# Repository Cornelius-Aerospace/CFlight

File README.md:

# CFlight
Experimental rocketry controller based on the esp8266 (esp01s), MPU6050 (accelerometer & gyroscope), Barometer (altitude) and small LiPo

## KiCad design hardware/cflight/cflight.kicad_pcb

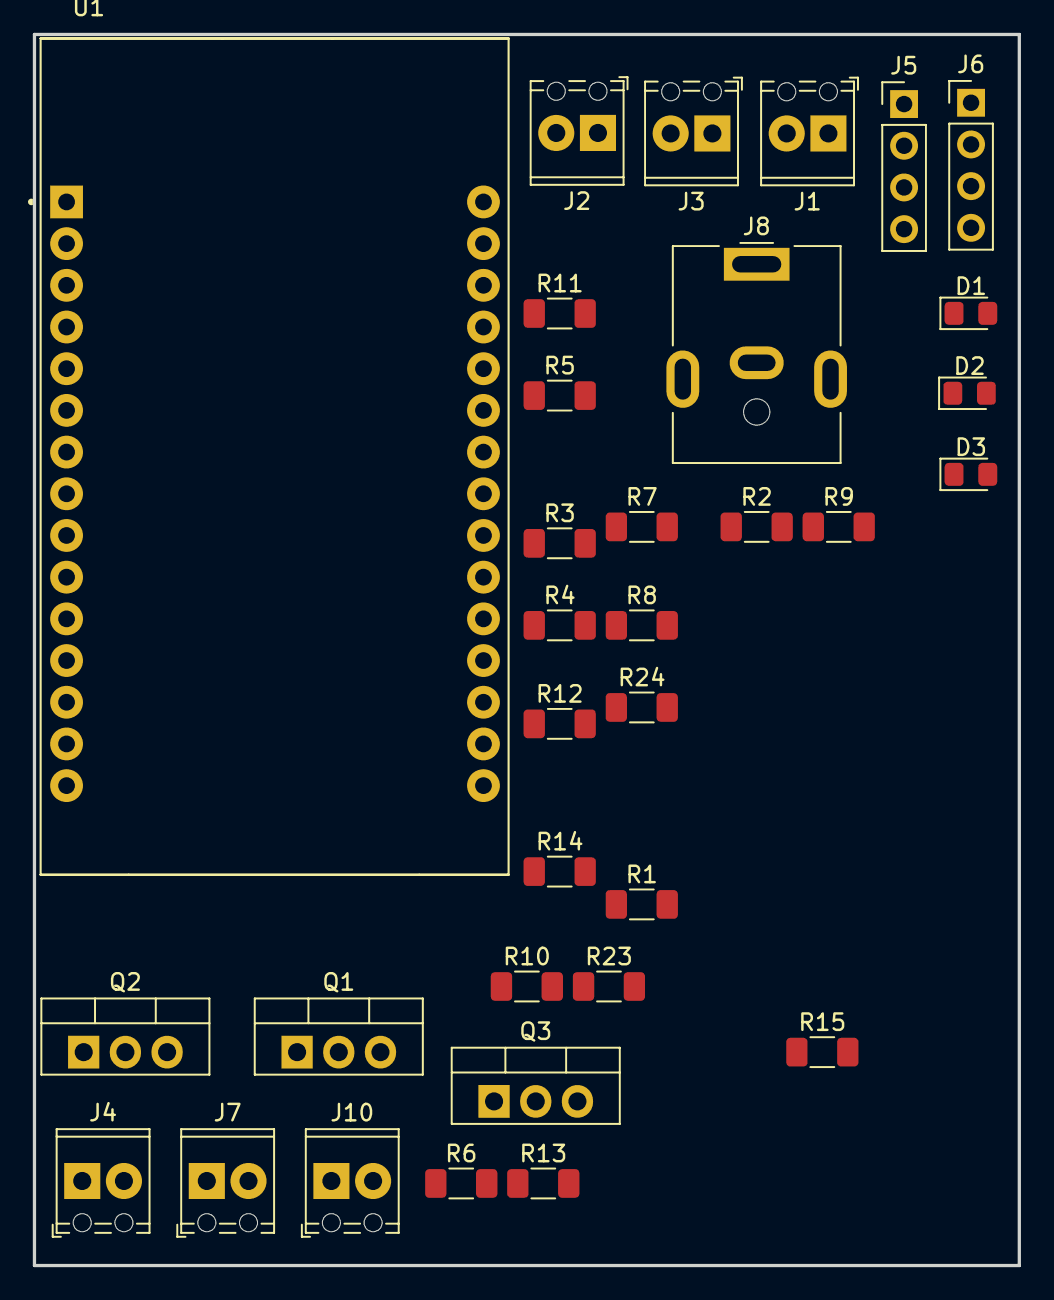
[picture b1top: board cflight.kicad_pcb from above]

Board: 2 copper layers, 60.0 x 75.0 mm, 33 parts (0 on the bottom side), 26 nets, no tracks yet.

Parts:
D1: Armed; LED_0805_2012Metric_Pad1.15x1.40mm_HandSolder
D2: Error; LED_0805_2012Metric_Pad1.15x1.40mm_HandSolder
D3: Status; LED_0805_2012Metric_Pad1.15x1.40mm_HandSolder
J1: 7.2v; TerminalBlock_Phoenix_MPT-0,5-2-2.54_1x02_P2.54mm_Horizontal
J2: I2C; TerminalBlock_Phoenix_MPT-0,5-2-2.54_1x02_P2.54mm_Horizontal
J3: 3.3v; TerminalBlock_Phoenix_MPT-0,5-2-2.54_1x02_P2.54mm_Horizontal
J4: CH_{1}; TerminalBlock_Phoenix_MPT-0,5-2-2.54_1x02_P2.54mm_Horizontal
J5: GPS; PinHeader_1x04_P2.54mm_Vertical
J6: GPRS; PinHeader_1x04_P2.54mm_Vertical
J7: CH_{3}; TerminalBlock_Phoenix_MPT-0,5-2-2.54_1x02_P2.54mm_Horizontal
J8: Barrel_Jack_Switch; BarrelJack_CUI_PJ-063AH_Horizontal
J10: CH_{2}; TerminalBlock_Phoenix_MPT-0,5-2-2.54_1x02_P2.54mm_Horizontal
Q1, Q2, Q3: TIP122; TO-220-3_Vertical
R1, R6, R12: 10k; R_1206_3216Metric_Pad1.30x1.75mm_HandSolder
R2: 18k; R_1206_3216Metric_Pad1.30x1.75mm_HandSolder
R3, R4, R11: 5k; R_1206_3216Metric_Pad1.30x1.75mm_HandSolder
R5: 12k; R_1206_3216Metric_Pad1.30x1.75mm_HandSolder
R7, R15: 80; R_1206_3216Metric_Pad1.30x1.75mm_HandSolder
R8, R14, R24: 470; R_1206_3216Metric_Pad1.30x1.75mm_HandSolder
R9: 50; R_1206_3216Metric_Pad1.30x1.75mm_HandSolder
R10, R13, R23: 4k7; R_1206_3216Metric_Pad1.30x1.75mm_HandSolder
U1: ESP32-DEVKIT-V1; MODULE_ESP32_DEVKIT_V1

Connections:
+3.3V: J3.1, J5.1, J6.1, U1.1 (3V3)
BATT_{check}: R2.2, R5.2, U1.25 (D27)
Batt_{gnd}: D1.1 (K), D2.1 (K), D3.1 (K), J1.2, J3.2, J5.2, J6.2, Q1.3 (E), Q2.3 (E), Q3.3 (E), R3.1, R4.1, R5.1, R10.2, R11.1, R13.2, R23.2, U1.2 (GND), U1.29 (GND)
CH_{1}^{fire}: R8.2, U1.21 (D32)
CH_{1}^{test}: R1.1, R3.2, U1.22 (D33)
CH_{2}^{fire}: R24.2, U1.20 (D35)
CH_{2}^{test}: R4.2, R6.1, U1.19 (D34)
CH_{3}^{fire}: R14.2, U1.28 (D13)
CH_{3}^{test}: R11.2, R12.1, U1.27 (D12)
LED_{error}: R9.2, U1.24 (D26)
LED_{status}: R7.2, U1.23 (D25)
unnamed: D1.2 (A), R15.1
unnamed: D2.2 (A), R7.1
unnamed: D3.2 (A), R9.1
unnamed: J4.2, Q2.2 (C), R1.2
unnamed: J7.2, Q3.2 (C), R12.2
unnamed: J10.2, Q1.2 (C), R6.2
unnamed: Q1.1 (B), R23.1, R24.1
unnamed: Q2.1 (B), R8.1, R10.1
unnamed: Q3.1 (B), R13.1, R14.1
Rx_{1}: J5.4, J6.4, U1.5 (D4), U1.6 (RX2)
SCL: J2.1, U1.14 (D22)
SDA: J2.2, U1.11 (D21)
Tx_{2}: J5.3, J6.3, U1.7 (TX2)
V_{arm}: J4.1, J7.1, J10.1, R15.2
V_{batt}: J1.1, J8.2, R2.1, U1.30 (VIN)

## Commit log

2023-07-05 Added readme
2023-07-05 "working" prototype
2023-08-18 Working POC
2023-09-10 Stuff
2023-09-11 SD card
2023-09-11 Works
2023-09-12 college
2023-09-12 Evening
2023-09-15 Restructure + add hardware
2023-09-18 Start segmenting code
2023-09-19 college prog
2023-09-29 Home 29/09/23 dajabo0ooooo
2023-10-03 Begin moving settings to be more OOP
2023-10-12 Move to new arcitecutre (rtos)
2023-10-12 Continue hardware
2024-10-09 Fixing Compile Errors TODO: in comms.cpp use SysSettings (from main.h/cpp)
2024-10-16 Continue Fixing bugs
2025-01-20 sync
2025-01-20 NV memory code
2025-01-20 Fixing this absolute linking mess :(
2025-01-29 Begin moving to FatFs
